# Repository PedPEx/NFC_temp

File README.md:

# Forked project "NFC_temp" (WIP!)
This is a NFC keychain which gets its power from the NFC reader and returns the measured temperature. There is also a article by the creator of this project over at [hackster.io](https://www.hackster.io/news/this-energy-harvesting-keychain-accessory-takes-temperatures-at-the-tap-of-a-smartphone-b571e382904c) 

## Used Components
- ATtiny1626 microcontroller (QFN20)
- RF430CL330HIRG NFC transponder (VQFN16)
- TMP117A ambient temperature sensor (DSBGA6)

## BOM
[Online BOM](https://htmlpreview.github.io/?https://raw.githubusercontent.com/PedPEx/NFC_temp/main/hardware/bom/html-bom.html)

[BOM](https://github.com/PedPEx/NFC_temp/tree/main/hardware/bom/BOM.csv)

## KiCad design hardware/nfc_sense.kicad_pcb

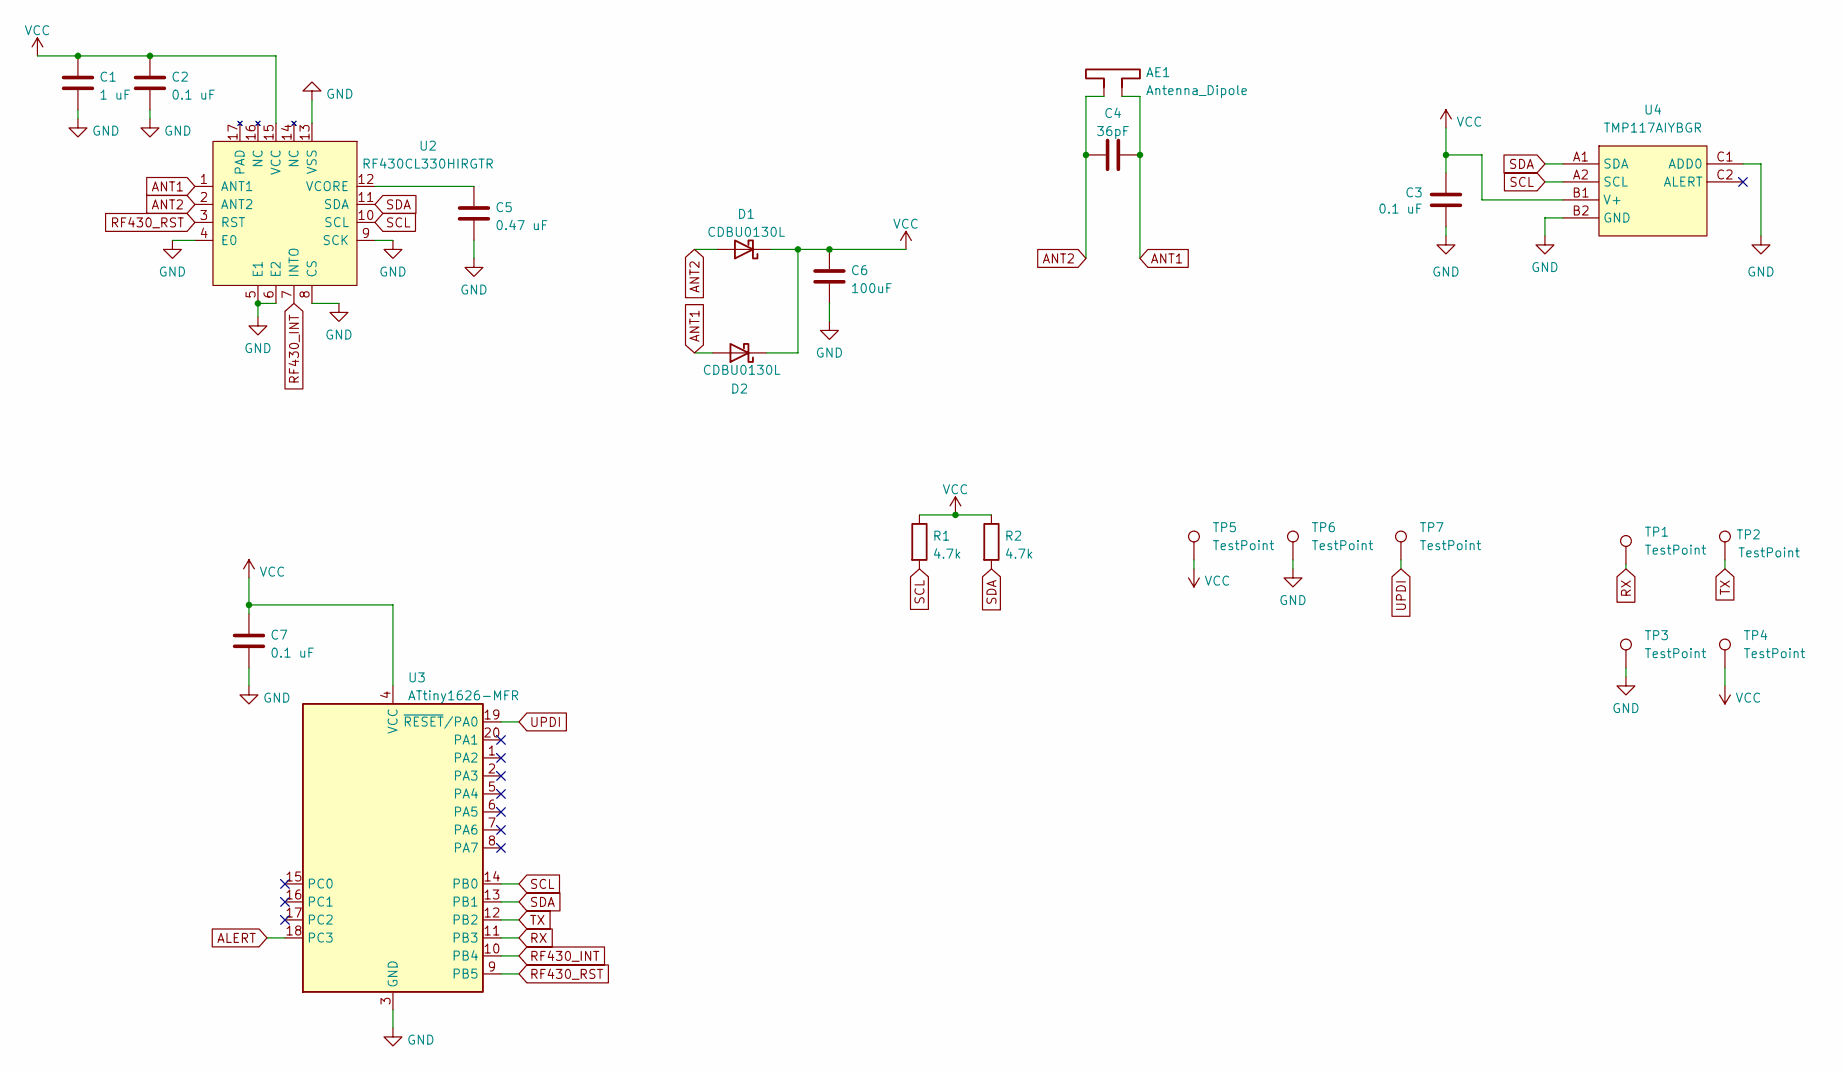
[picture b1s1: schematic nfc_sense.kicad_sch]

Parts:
AE1: Antenna_Dipole; 35_18_1_9nH
C1: 1 uF; C_0603_1608Metric
C2, C7: 0.1 uF; C_0603_1608Metric
C3: 0.1 uF; C_0402_1005Metric
C4: 36pF; C_0402_1005Metric
C5: 0.47 uF; C_0603_1608Metric
C6: 100uF; C_1206_3216Metric
D1, D2: CDBU0130L; D_0603_1608Metric_Pad1.05x0.95mm_HandSolder
R1, R2: 4.7k; R_0603_1608Metric_Pad0.98x0.95mm_HandSolder
TP1, TP2, TP3, TP4, TP5, TP6, TP7: TestPoint; TestPoint_Pad_D1.0mm
U2: RF430CL330HIRGTR‎; VQFN-16_L3.0-W3.0-P0.50-BL-EP1.7
U3: ATtiny1626-MFR; QFN-20_L3.0-W3.0-P0.40-BL-EP1.7
U4: TMP117AIYBGR; DSBGA-6_L1.5-W1.0-R3-C2-P0.40-TL; LCSC Part C2871893

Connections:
ALERT: U3.18 (PC3)
ANT1: AE1.1, C4.2, D2.2 (A), U2.1 (ANT1)
ANT2: AE1.2, C4.1, D1.2 (A), U2.2 (ANT2)
GND: C1.2, C2.2, C3.2, C5.2, C6.2, C7.2, TP3.1, TP6.1, U2.4 (E0), U2.5 (E1), U2.6 (E2), U2.8 (CS), U2.9 (SCK), U2.13 (VSS), U3.3 (GND), U3.21 (GND), U4.B2 (GND), U4.C1 (ADD0)
unnamed: C5.1, U2.12 (VCORE)
RF430_INT: U2.7 (INTO), U3.10 (PB4)
RF430_RST: U2.3 (RST), U3.9 (PB5)
RX: TP1.1, U3.11 (PB3)
SCL: R1.2, U2.10 (SCL), U3.14 (PB0), U4.A2 (SCL)
SDA: R2.2, U2.11 (SDA), U3.13 (PB1), U4.A1 (SDA)
TX: TP2.1, U3.12 (PB2)
UPDI: TP7.1, U3.19 (~RESET/PA0)
VCC: C1.1, C2.1, C3.1, C6.1, C7.1, D1.1 (K), D2.1 (K), R1.1, R2.1, TP4.1, TP5.1, U2.15 (VCC), U3.4 (VCC), U4.B1 (V+)

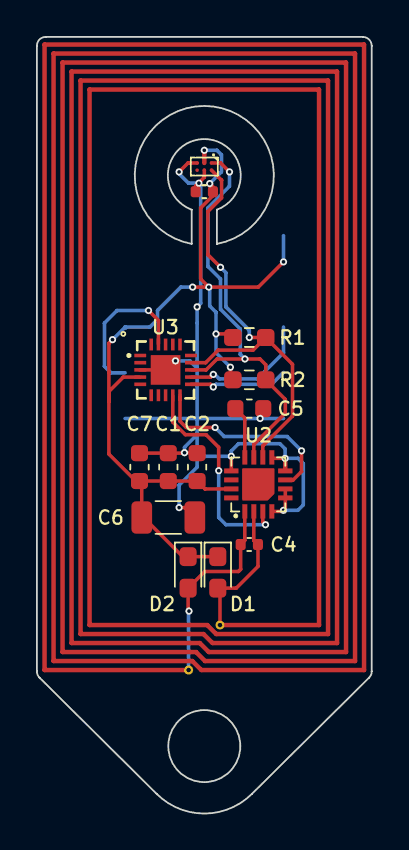
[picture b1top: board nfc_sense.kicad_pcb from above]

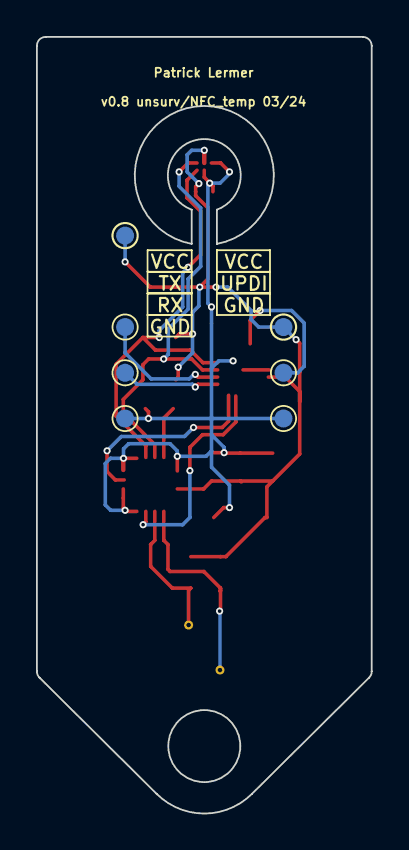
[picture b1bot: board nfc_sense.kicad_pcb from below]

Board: 2 copper layers, 18.6 x 43.1 mm, 22 parts (7 on the bottom side), 12 nets.

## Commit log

2024-04-20 init own repo
2024-04-20 fixed mistake in README
